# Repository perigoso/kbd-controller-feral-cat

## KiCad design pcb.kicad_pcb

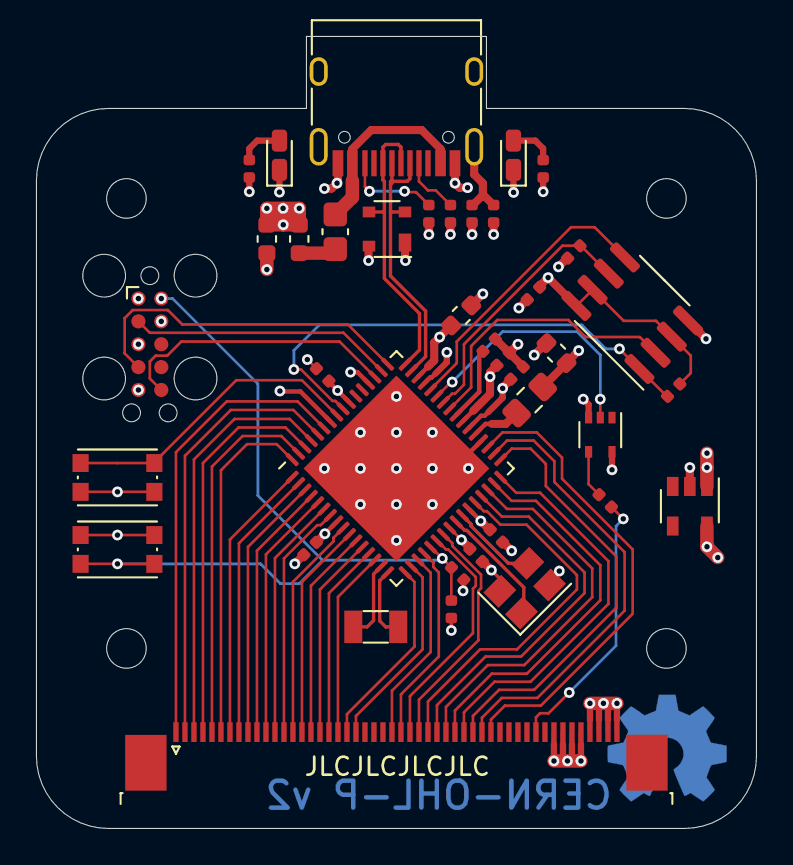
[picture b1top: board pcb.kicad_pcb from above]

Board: 4 copper layers, 40.0 x 44.0 mm, 39 parts (0 on the bottom side), 66 nets.

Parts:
C1, C2, C3, C4, C5, C8, C10, C14: 100nF; C_0402_1005Metric
C7: 10uF; C_0603_1608Metric
C9: 4.7nF; C_0402_1005Metric
C11, C12: 4.7uF; C_0603_1608Metric
C13: 1uF; C_0402_1005Metric
D1, D2: LED; LED_0603_1608Metric_Castellated
D3: PRTR5V0U2X; SOT-143
F1: Polyfuse; Fuse_0805_2012Metric_Castellated
FB1: Ferrite_Bead_Small; L_0603_1608Metric
J1: USB_C_Receptacle_USB2.0; USB_C_Receptacle_HRO_TYPE-C-31-M-12
J2: Conn_ARM_JTAG_SWD_10; Tag-Connect_TC2050-IDC-FP_2x05_P1.27mm_Vertical
J3: Conn_02x25_Counter_Clockwise; TE_5-1734839-0_1x50-1MP_P0.5mm_Horizontal
L1: 4.7uH; L_0805_2012Metric_Pad1.15x1.40mm_HandSolder
R1, R2: 1k; R_0402_1005Metric
R3: 100; R_0402_1005Metric
R5, R6, R10: 10k; R_0402_1005Metric
R7, R8: 5.1k; R_0402_1005Metric
R9: 1M; R_0402_1005Metric
SW1, SW2: SW_Push; SW_Push_1P1T_NO_CK_KMR2
U1: 25CSM04; SOIC-8_3.9x4.9mm_P1.27mm
U2: EFM32GG11B8xx-QFN64; QFN-64-1EP_9x9mm_P0.5mm_EP7.3x7.3mm
U3: 74LVC1G17; SOT-353_SC-70-5
U4: MIC2003; SOT-23-5
Y1: 32.768KHz; Crystal_SMD_3215-2Pin_3.2x1.5mm
Y2: 8MHz; Crystal_SMD_3225-4Pin_3.2x2.5mm

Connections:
+1V8: C4.2, C12.2, L1.1, U2.39
+3V3: C1.2, C2.2, C3.2, C5.2, C8.2, C11.2, C14.2, J2.1, R2.2, R6.2, R10.2, U1.3, U1.7, U1.8, U2.8, U2.24, U2.27, U2.38, U2.46, U2.55
+5V: C7.2, D3.4, FB1.2, R1.2, U2.45, U2.52, U3.5, U4.1
/COL0: J3.25, U2.19
/COL1: J3.26, U2.20
/COL2: J3.27, U2.22
/COL3: J3.28, U2.23
/COL4: J3.29, U2.28
/COL5: J3.30, U2.29
/COL6: J3.31, U2.30
/COL7: J3.32, U2.31
/COL8: J3.33, U2.32
/COL9: J3.34, U2.33
/COL10: J3.35, U2.34
/COL11: J3.36, U2.35
/EEPROM_MISO: U1.2, U2.41
/EEPROM_MOSI: U1.5, U2.44
/EEPROM_SCLK: R5.2, U1.6, U2.42
/EEPROM_~CS: R6.1, U1.1, U2.56
/HF_XTAL_N: U2.25, Y2.1
/HF_XTAL_P: U2.26, Y2.3
/LED_DAT1: J3.41, R3.1
/LF_XTAL_N: U2.16, Y1.2
/LF_XTAL_P: U2.15, Y1.1
/MCU_LED_DAT1: U2.43, U3.2
/ROW0: J3.1, U2.59
/ROW1: J3.2, U2.60
/ROW2: J3.3, U2.61
/ROW3: J3.4, U2.62
/ROW4: J3.5, U2.63
/ROW5: J3.6, U2.64
/ROW6: J3.7, U2.1
/ROW7: J3.8, U2.2
/ROW8: J3.9, U2.3
/ROW9: J3.10, U2.4
/ROW10: J3.11, U2.5
/ROW11: J3.12, U2.6
/ROW12: J3.13, U2.7
/ROW13: J3.14, U2.9
/ROW14: J3.15, U2.10
/ROW15: J3.16, U2.11
/ROW16: J3.17, U2.12
/ROW17: J3.18, U2.13
/ROW18: J3.19, U2.14
/ROW19: J3.20, U2.17
/ROW20: J3.21, U2.18
/SWCLK: J2.4, U2.49
/SWDIO: J2.2, U2.50
/SWO: J2.6, U2.51
/USB_CC1: J1.A5, R8.2
/USB_CC2: J1.B5, R7.2
/USB_D_N: D3.2, J1.A7, J1.B7, U2.47
/USB_D_P: D3.3, J1.A6, J1.B6, U2.48
/USB_SH: C9.2, J1.S1, R9.2
/USER_BTN: SW1.2, U2.57
/VBUS: F1.1, J1.A4, J1.A9, J1.B4, J1.B9
/VBUS_FUSED: F1.2, FB1.1
/VREGSW: L1.2, U2.37
/~RESET: C10.2, J2.10, R10.1, SW2.1, U2.21
/~STATE_LED: D2.1, U2.58
GND: C1.1, C2.1, C3.1, C4.1, C5.1, C7.1, C8.1, C9.1, C10.1, C11.1, C12.1, C13.1, C14.1, D1.1, D3.1, J1.A1, J1.A12, J1.B1, J1.B12, J2.3, J2.5, J2.9, J3.43, J3.44, J3.45, J3.46, R5.1, R7.1, R8.1, R9.1, SW1.1, SW2.2, U1.4, U2.36, U2.65, U3.3, U4.2, Y2.2, Y2.4
unnamed: C13.2, U2.40
unnamed: D1.2, R1.1
unnamed: D2.2, R2.1
unnamed: J3.47, J3.48, J3.49, J3.50, U4.5
unnamed: R3.2, U3.4

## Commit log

2020-09-23 production ready
2020-09-23 production fixes

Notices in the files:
pcb.kicad_pcb:
Licensed under CERN Open Hardware Licence v2 Permissive
CERN-OHL-P v2
